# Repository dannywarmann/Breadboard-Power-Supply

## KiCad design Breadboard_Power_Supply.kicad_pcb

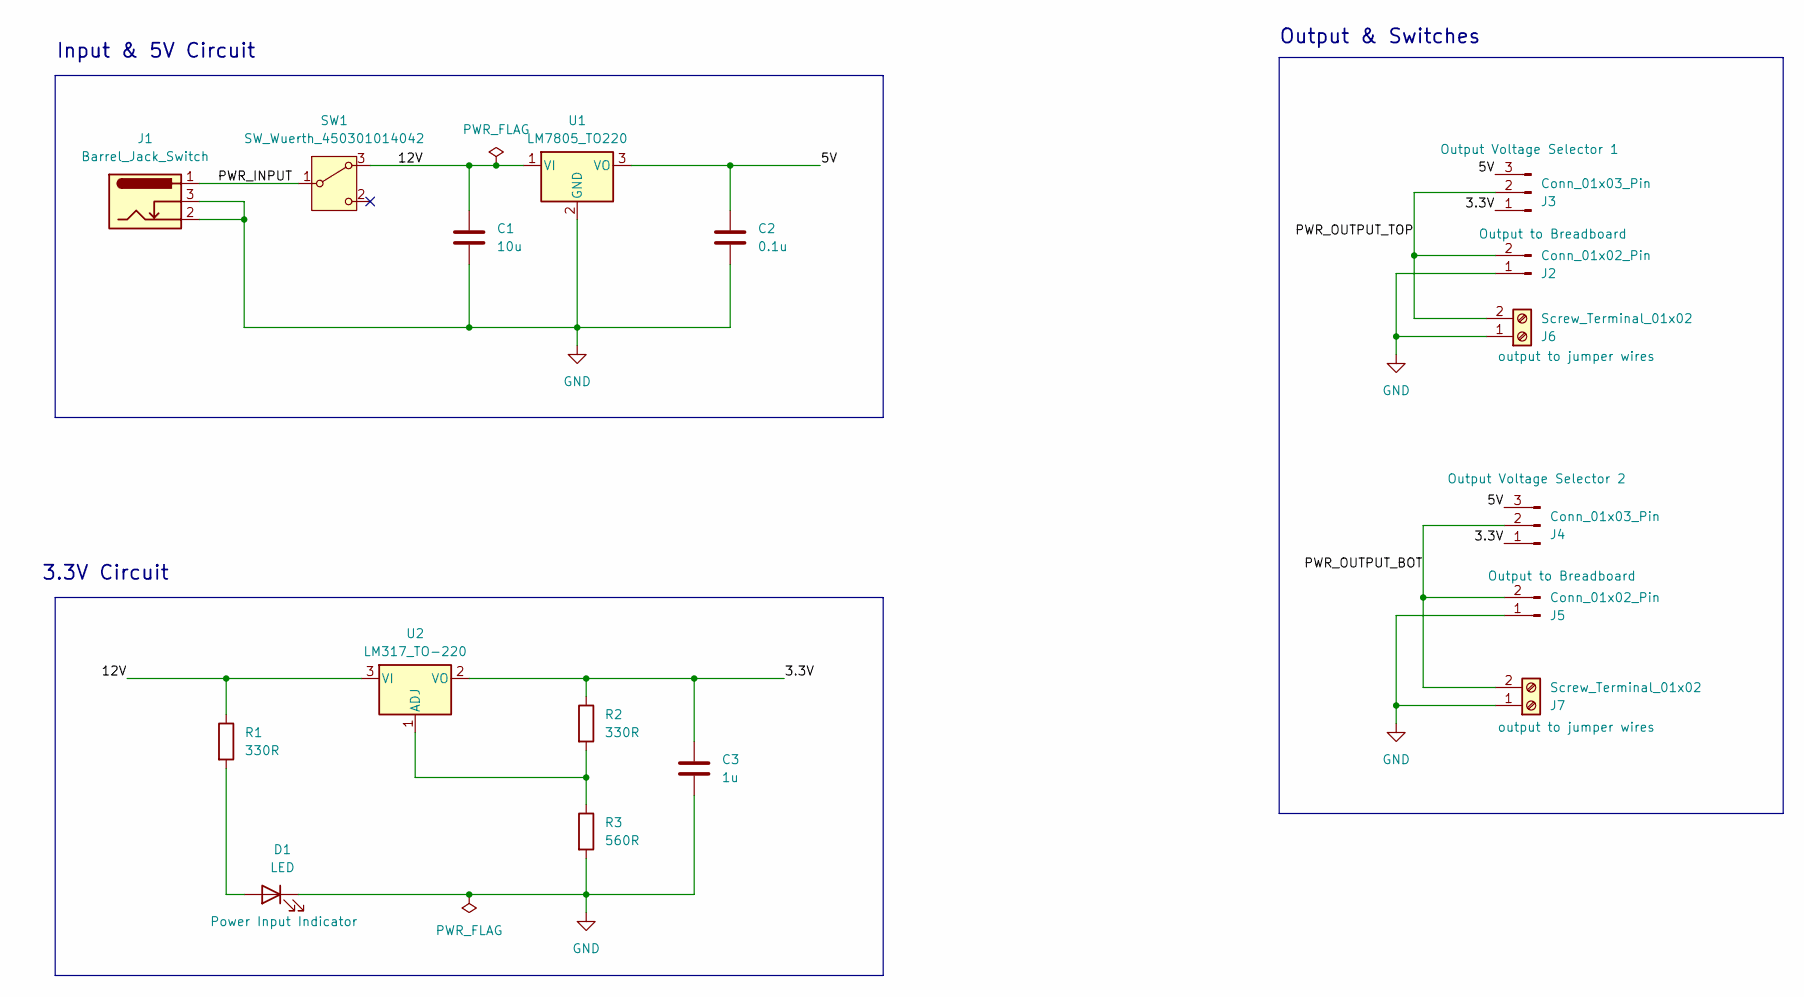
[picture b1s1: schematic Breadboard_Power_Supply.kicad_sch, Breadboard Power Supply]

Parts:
C1: 10u; C_Disc_D3.0mm_W1.6mm_P2.50mm
C2: 0.1u; C_Disc_D3.0mm_W1.6mm_P2.50mm
C3: 1u; C_Disc_D3.0mm_W1.6mm_P2.50mm
D1: LED; LED_D5.0mm
J1: Barrel_Jack_Switch; BarrelJack_Horizontal
J2, J5: Conn_01x02_Pin; PinHeader_1x02_P2.54mm_Vertical
J3, J4: Conn_01x03_Pin; PinHeader_1x03_P2.54mm_Vertical
J6, J7: Screw_Terminal_01x02; TerminalBlock_Phoenix_MKDS-1,5-2-5.08_1x02_P5.08mm_Horizont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
R1, R2: 330R; R_Axial_DIN0204_L3.6mm_D1.6mm_P7.62mm_Horizontal
R3: 560R; R_Axial_DIN0204_L3.6mm_D1.6mm_P7.62mm_Horizontal
SW1: SW_Wuerth_450301014042; SW_Slide-03_Wuerth-WS-SLTV_10x2.5x6.4_P2.54mm
U1: LM7805_TO220; TO-220-3_Vertical
U2: LM317_TO-220; TO-220-3_Vertical

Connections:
/3.3V: C3.1, J3.1, J4.1, R2.1, U2.2 (VO)
/5V: C2.1, J3.3, J4.3, U1.3 (VO)
/12V: C1.1, R1.1, SW1.3 (A), U1.1 (VI), U2.3 (VI)
/PWR_INPUT: J1.1, SW1.1 (B)
/PWR_OUTPUT_BOT: J4.2, J5.2, J7.2
/PWR_OUTPUT_TOP: J2.2, J3.2, J6.2
GND: C1.2, C2.2, C3.2, D1.1 (K), J1.2, J1.3, J2.1, J5.1, J6.1, J7.1, R3.2, U1.2 (GND)
unnamed: D1.2 (A), R1.2
unnamed: R2.2, R3.1, U2.1 (ADJ)

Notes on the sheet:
Output & Switches
Input & 5V Circuit
3.3V Circuit

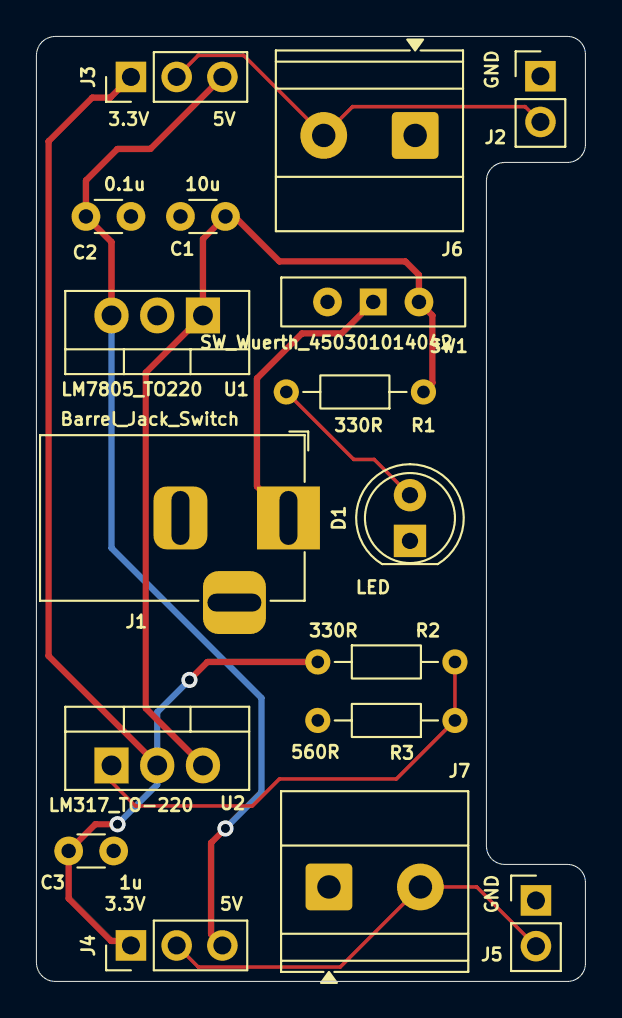
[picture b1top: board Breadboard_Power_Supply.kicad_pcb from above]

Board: 2 copper layers, 30.5 x 52.5 mm, 17 parts (0 on the bottom side), 9 nets.
